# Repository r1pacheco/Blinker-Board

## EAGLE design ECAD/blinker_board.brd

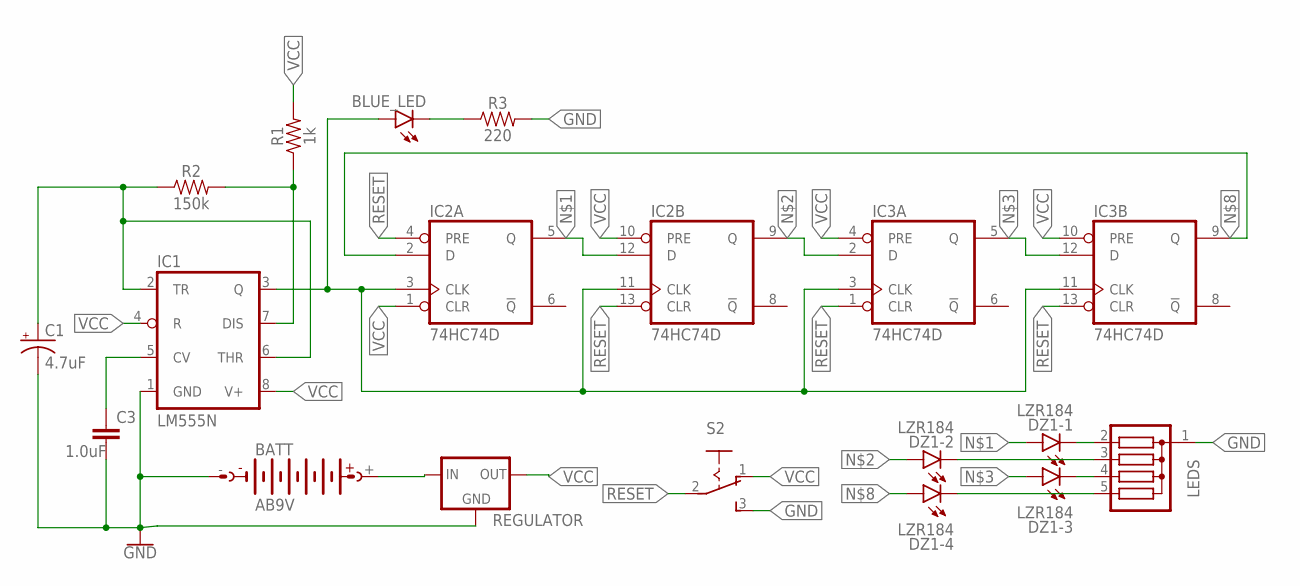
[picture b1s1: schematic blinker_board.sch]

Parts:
BATT: AB9V
BLUE_LED: LED; SMARTLED-TTW
C1: 4.7uF; A/3216-18R
C3: 1.0uF; 0402
DZ1: LZR184
IC1: LM555N; DIL08
IC2, IC3: 74HC74D; SO14
LEDS: G04R; SIL5
R1: 1k; 0603
R2: 150k; 0603
R3: 220; 0603
REGULATOR: 78MXXS
S2: 255SB

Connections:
GND: BATT.-, C1.-, C3.2, IC1.1 (GND), IC2.7 (GND), IC3.7 (GND), LEDS.1, R3.2, REGULATOR.GND, S2.3 (S)
unnamed: DZ1.A1 (A), IC2.5 (Q), IC2.12 (D)
unnamed: DZ1.A2 (A), IC2.9 (Q), IC3.2 (D)
unnamed: DZ1.A3 (A), IC3.5 (Q), IC3.12 (D)
unnamed: BLUE_LED.A@1 (A), IC1.3 (Q), IC2.3 (CLK), IC2.11 (CLK), IC3.3 (CLK), IC3.11 (CLK)
unnamed: BATT.+, REGULATOR.IN
unnamed: DZ1.K1 (C), LEDS.2
unnamed: DZ1.K2 (C), LEDS.3
unnamed: DZ1.A4 (A), IC2.2 (D), IC3.9 (Q)
unnamed: DZ1.K3 (C), LEDS.4
unnamed: DZ1.K4 (C), LEDS.5
unnamed: C3.1, IC1.5 (CV)
unnamed: IC1.7 (DIS), R1.1, R2.2
unnamed: BLUE_LED.C@1 (C), R3.1
unnamed: C1.+, IC1.2 (TR), IC1.6 (THR), R2.1
RESET: IC2.4 (PRE), IC2.13 (CLR), IC3.1 (CLR), IC3.13 (CLR), S2.2
VCC: IC1.4 (R), IC1.8 (V+), IC2.1 (CLR), IC2.10 (PRE), IC2.14 (VCC), IC3.4 (PRE), IC3.10 (PRE), IC3.14 (VCC), R1.2, REGULATOR.OUT, S2.1 (O)

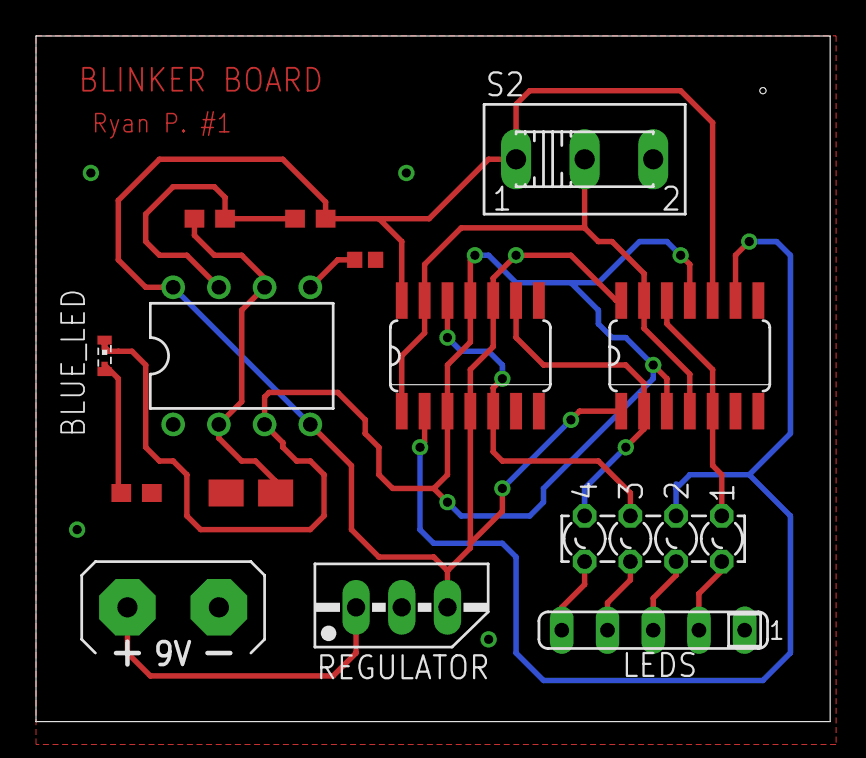
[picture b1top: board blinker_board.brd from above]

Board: 2 copper layers, 44.1 x 38.1 mm, 14 parts (0 on the bottom side), 17 nets.

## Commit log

2021-10-03 Upload all files

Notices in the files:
parts and their libraries:
SparkFun-Capacitors: Licensing: Creative Commons ShareAlike 4.0 International - https://creativecommons.org/licenses/by-sa/4.0
